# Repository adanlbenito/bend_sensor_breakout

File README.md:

# Bend Sensor Breakout Board for String Instruments

Breakout board Kicad design files for guitar string bend sensors based on [NVE AAT001](https://www.nve.com/angleSensors) Tunnel Magnetoresistive angle sensing technology

The board integrates an AAT001 sensor and an amplifier for both _sine_ and _cosine_ componets and is supposed to be used in conjunction with [N42 neodymium magnets](https://www.first4magnets.com/circular-disc-rod-c34/4mm-dia-x-3mm-thick-n42-neodymium-magnet-0-54kg-pull-p3049#ps_0_3096|ps_1_16682). Design files for laser cutting a magnet holder for 3x4mm magnets suitable for an electric guitar with string spacing of 52mm have been included.

## License
These hardware designs are licensed under a [Creative Commons Attribution-Sharealike](https://creativecommons.org/licenses/by-sa/3.0/) license, or [CC-BY-SA](https://creativecommons.org/licenses/by-sa/3.0/).

> Adan L. Benito Temprano and Andrew P. McPherson. _A TMR Angle Sensor for Gesture Acquisition and Disambiguation on the Electric Guitar_. In Proceedings of the International Audio Mostly Conference on Sonic experiences in the era of the Internet of Sounds, September 1-3, 2021, Trento, Italy.
`

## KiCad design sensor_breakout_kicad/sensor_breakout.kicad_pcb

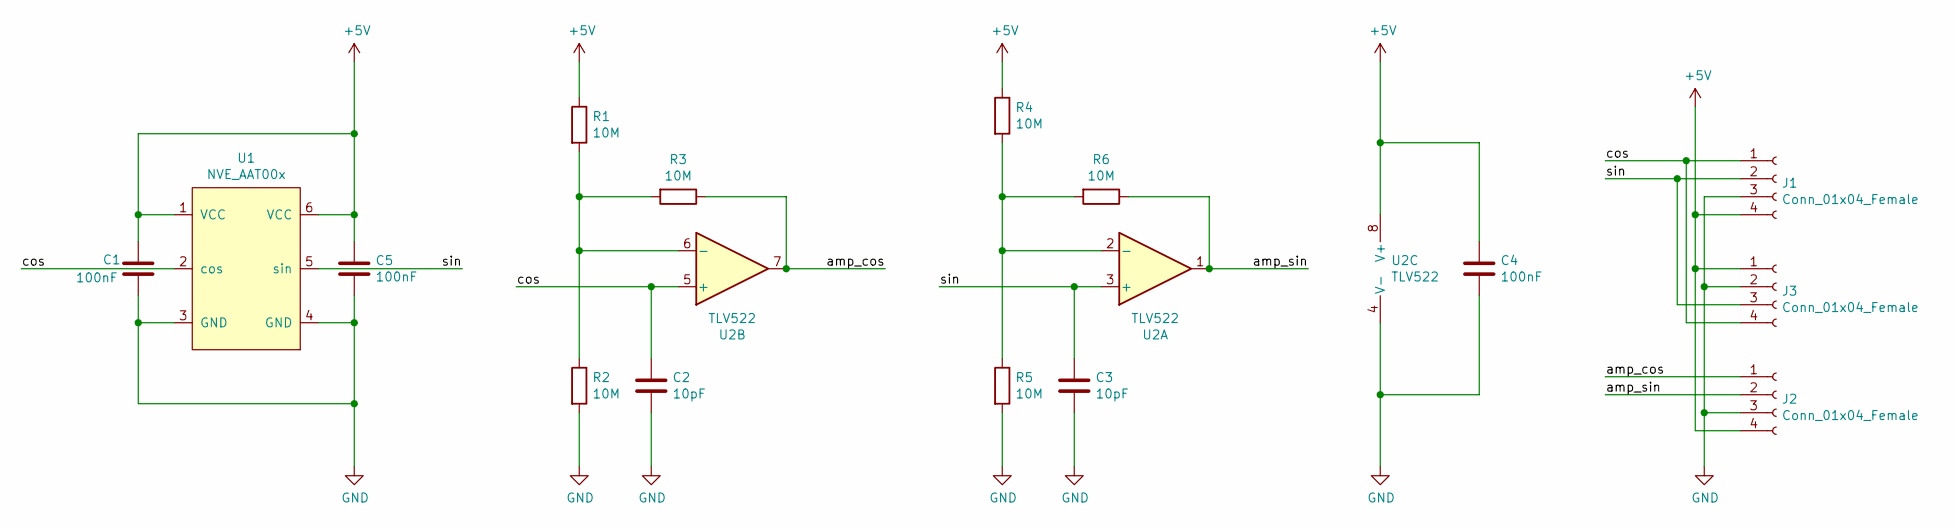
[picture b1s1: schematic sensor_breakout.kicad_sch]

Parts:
C1, C4, C5: 100nF; C_0603_1608Metric
C2, C3: 10pF; C_0603_1608Metric
J1, J2, J3: Conn_01x04_Female; JST_PH_S4B-PH-SM4-TB_1x04-1MP_P2.00mm_Horizontal
R1, R2, R3, R4, R5, R6: 10M; R_0603_1608Metric
U1: NVE_AAT00x; TDFN-6-1EP_2.5x2.5mm_P0.65mm_EP1.3x2mm_ThermalVias
U2: TLV522; TSSOP-8_3x3mm_P0.65mm

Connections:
+5V: C1.1, C4.1, C5.1, J1.4, J2.4, J3.1, R1.1, R4.1, U1.1 (VCC), U1.6 (VCC), U2.8 (V+)
/amp_cos: J2.1, R3.1, U2.7
/amp_sin: J2.2, R6.1, U2.1
/cos: C2.1, J1.1, J3.4, U1.2 (cos), U2.5 (+)
/sin: C3.1, J1.2, J3.3, U1.5 (sin), U2.3 (+)
GND: C1.2, C2.2, C3.2, C4.2, C5.2, J1.3, J2.3, J3.2, R2.2, R5.2, U1.3 (GND), U1.4 (GND), U2.4 (V-)
unnamed: R1.2, R2.1, R3.2, U2.6 (-)
unnamed: R4.2, R5.1, R6.2, U2.2 (-)

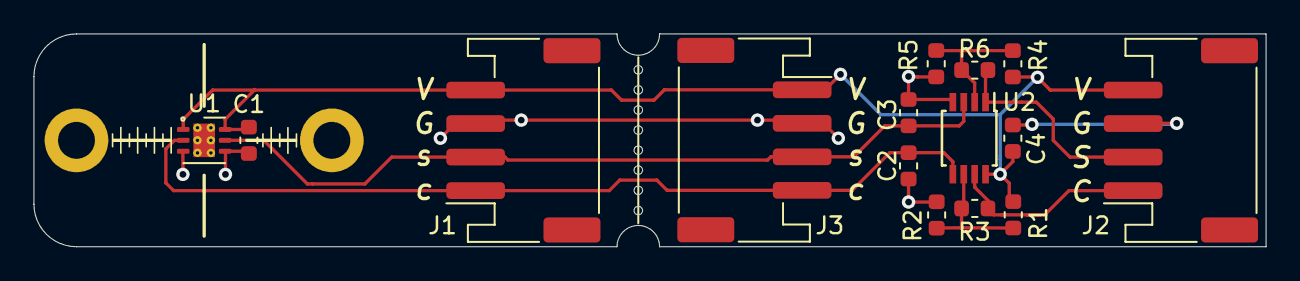
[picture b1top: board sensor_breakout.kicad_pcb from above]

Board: 2 copper layers, 73.5 x 12.7 mm, 15 parts (0 on the bottom side), 8 nets.

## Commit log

2021-07-26 Added Kicad files
2021-07-26 Added magnet holder laser cutting files
2021-07-26 Added license blurb
